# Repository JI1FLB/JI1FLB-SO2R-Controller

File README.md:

# JI1FLB-SO2R-Controller

This JI1FLB SO2R box (controller) is a tool for amateur radio contest and works with OTRPS protocol.
This device controls two amateur radio rigs and is programmed with Arduino UNO sketch.
Hardware was composed of circuits that are easily available at electronic parts stores.
In addition, each circuit is designed to PCB to ensure ease of manufacture and product stability.

This JI1FLB　SO2R box (controller) provides software and hardware as freeware subject to non-commercial use.
Hardware PCB board is scheduled to provide KiCAD data subject to non-commercial use after completion of reprocessing.
I will supply the PCB to those who need it, with shipping fee and very cheap actual expenses. 
However, some consideration is required when installing some parts.

このJI1FLB　SO2Rボックス（コントローラ）は、アマチュア無線コンテスト用ツールでOTRPSプロトコロルで動作します。
この装置は、2台のアマチュア無線リグをコントロールするもので、ArduinoUNOのスケッチでプログラムされています。
ハードウェアは、電子パーツ店で容易に入手可能な部品で回路を構成しました。
また、各回路は、製作の容易性、製品の安定性を確保するため、PCB化を図っています。

このJI1FLB　SO2Rボックス（コントローラ）は、非商用利用を条件にソフトウェアとハードウェアをフリーウェアとして提供します。
ハードウェアのPCB基板は、KiCADデータを再作が完了後に、非商用利用を条件に提供する予定です。
私は、PCBを必要な方に、送料と非常に安価な実費で供給します。ただし、一部の部品を取り付け際に若干の考慮が必要です。

2018/11/18 Seiichi Tanaka 田中盛一

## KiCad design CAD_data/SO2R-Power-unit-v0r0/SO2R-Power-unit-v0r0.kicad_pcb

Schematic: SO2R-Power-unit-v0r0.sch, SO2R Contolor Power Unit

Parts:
C1, C5: 100uF; C_Radial_D10_L13_P5
C2, C3, C6, C7: 0.1uF; C_Rect_L7_W2_P5
C4: 56uF 25SEPF56M; C_Radial_D6.3_L11.2_P2.5
C8: 56uF; C_Radial_D6.3_L11.2_P2.5
D1: LED; LED-3MM
D6, D7: 1N4007; Diode_DO-41_SOD81_Horizontal_RM10
F1: RUEF185; C_Rect_L7_W3.5_P5
F2, F3: RXEF065; C_Rect_L7_W3.5_P5
F4, F5: RXEF110; C_Rect_L7_W3.5_P5
FI1: EMI_FILTER2; EMIFILTER
P1, P2, P3, P4, P5: CONN_01X02; CON-JST-B02B-XASK-1
R1: 2.2K; Resistor_Horizontal_RM7mm
U1, U2: LM7805CT; TO-220
VAR1: CNR07D151K; RV_Disc_D7_W3.4_P5
W1, W2, W3, W4, W5: TEST_1P; SolderWirePad_single_0-8mmDrill

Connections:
GND: C1.2, C2.2, C3.2, C4.2, C5.2, C6.2, C7.2, C8.2, D1.1 (K), FI1.2 (GND), P1.2, P2.2, P3.2, P4.2, P5.2, U1.2 (GND), U2.2 (GND), VAR1.2
unnamed: C1.1, C2.1, C5.1, C6.1, D6.1, D7.1, F5.1, FI1.3 (VO), U1.1 (IN), U2.1 (IN)
unnamed: C3.1, C4.1, D6.2, F2.1, F3.1, U1.3 (OUT)
unnamed: C7.1, C8.1, D7.2, F4.1, U2.3 (OUT)
unnamed: D1.2 (A), R1.2
unnamed: F1.1, P1.1
unnamed: F1.2, FI1.1 (VI), R1.1, VAR1.1, W1.1
unnamed: F2.2, P2.1, W2.1
unnamed: F3.2, P3.1, W3.1
unnamed: F4.2, P4.1, W4.1
unnamed: F5.2, P5.1, W5.1

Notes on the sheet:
7.62mm
8.89mm

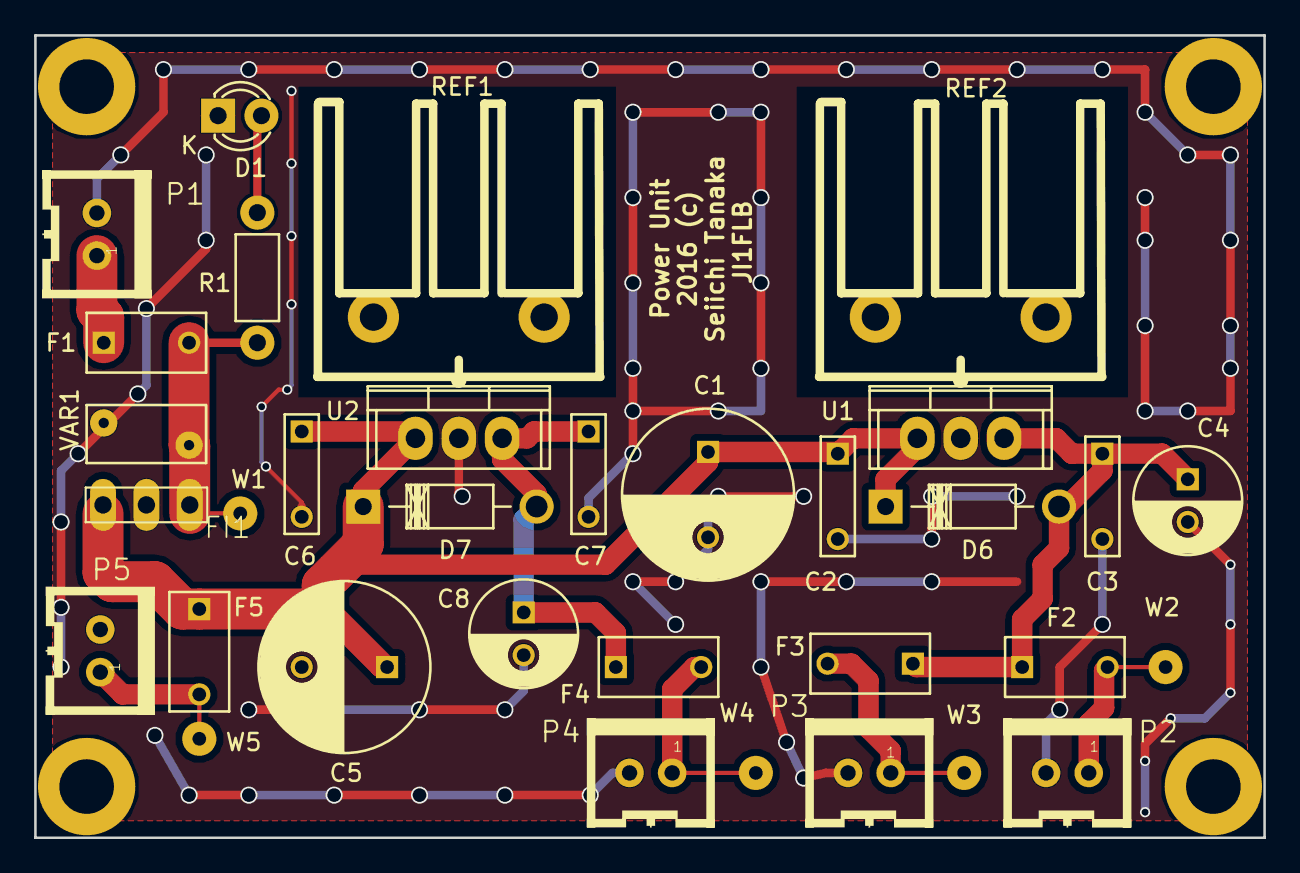
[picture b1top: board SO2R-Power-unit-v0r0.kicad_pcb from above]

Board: 2 copper layers, 72.0 x 47.0 mm, 33 parts (0 on the bottom side), 11 nets.

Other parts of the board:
REF1, REF2: Heatsink-16PB017

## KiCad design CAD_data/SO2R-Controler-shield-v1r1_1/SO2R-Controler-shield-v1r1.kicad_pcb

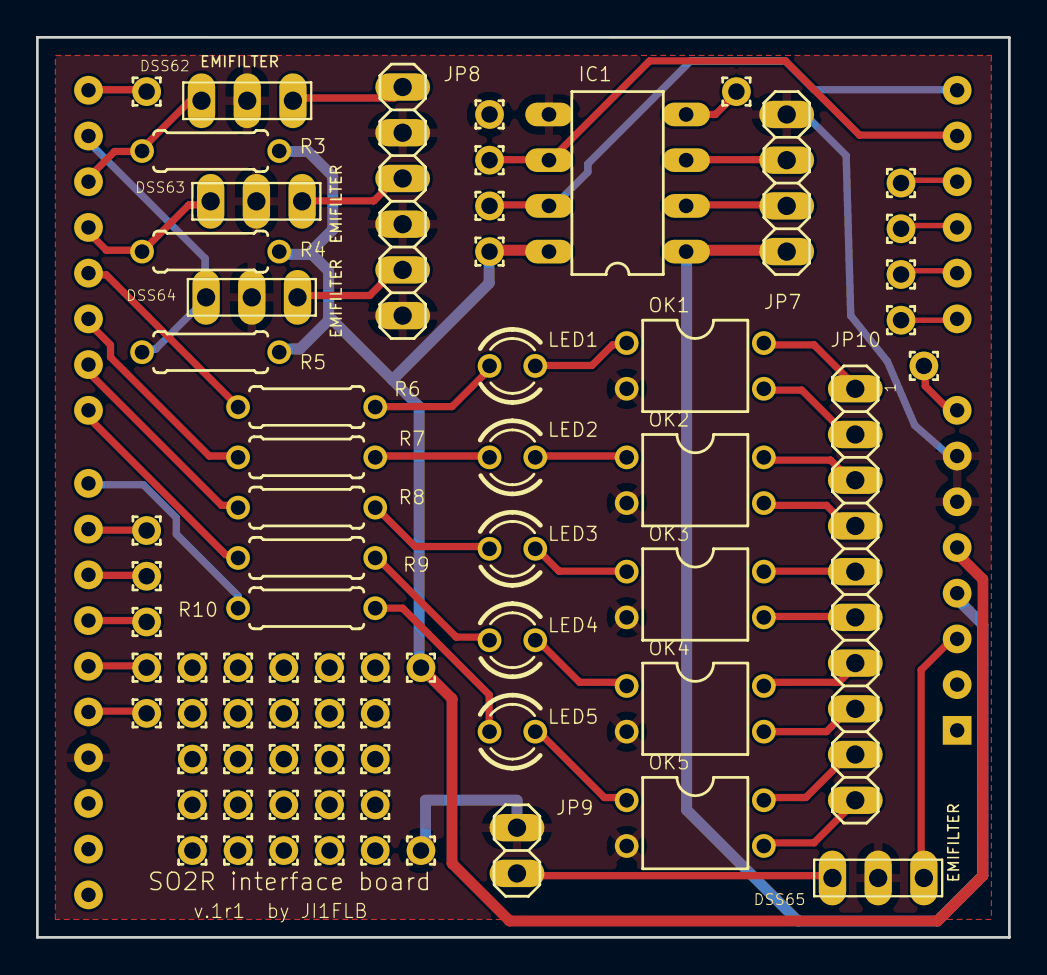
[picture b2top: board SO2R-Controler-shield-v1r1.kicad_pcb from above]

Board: 2 copper layers, 54.0 x 50.0 mm, 71 parts (0 on the bottom side), 52 nets.

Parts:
A1: Arduino_UNO_R3
DSS62, DSS63, DSS64, DSS65: EMIFILTER
IC1: AE-PCA9306; DIL8
JP7: I2C LCD; 1X04
JP8: Force Switch; 1X06
JP9: RESET; 1X02
JP10: Isolate port; 1X10
LED1, LED2, LED3, LED4, LED5: OSDR3133A; LED3MM
OK1, OK2, OK3, OK4, OK5: TLP621; DIL04
PAD1, PAD2, PAD3, PAD4, PAD5, PAD6, PAD7, PAD8, PAD9, PAD10, PAD11, PAD12, PAD13, PAD14, PAD15, PAD16, PAD17, PAD18, PAD19, PAD20, PAD21, PAD22, PAD23, PAD24, PAD25, PAD26, PAD27, PAD28, PAD29, PAD30, PAD31, PAD32, PAD33, PAD34, PAD35, PAD36, PAD37, PAD38, PAD39, PAD40, PAD41, PAD42, PAD43: 1,6_0,9
R3, R4, R5: 10K; 0207_7
R6, R7, R8, R9, R10: 330; 0207_7

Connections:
+3V3: A1.4, IC1.1, JP7.1
/D1: A1.16, DSS64.3, R5.1
/D2: A1.17, DSS62.3, R3.1
/D3: A1.18, DSS63.3, R4.1
/D4: A1.19, R6.1
/D5: A1.20, R7.1
/D6: A1.21, R8.1
/D7: A1.22, R9.1
/D8: A1.23, R10.1
/SCL5V: A1.14, IC1.7, PAD4.1
/SDA5V: A1.13, IC1.6, PAD5.1
GND1: A1.6, A1.7, A1.29, DSS62.2, DSS63.2, DSS64.2, DSS65.2, IC1.5, JP7.4, JP8.2, JP8.4, JP8.6, JP9.2, OK1.2, OK2.2, OK3.2, OK4.2, OK5.2, PAD6.1, PAD39.1
unnamed: A1.8, PAD1.1
unnamed: A1.9, PAD40.1
unnamed: A1.10, PAD41.1
unnamed: A1.11, PAD42.1
unnamed: A1.12, PAD43.1
unnamed: A1.15, PAD12.1
unnamed: A1.24, PAD11.1
unnamed: A1.25, PAD10.1
unnamed: A1.26, PAD9.1
unnamed: A1.27, PAD8.1
unnamed: A1.28, PAD7.1
unnamed: DSS62.1, JP8.1
unnamed: DSS63.1, JP8.3
unnamed: DSS64.1, JP8.5
unnamed: DSS65.1, JP9.1
unnamed: IC1.2, JP7.2
unnamed: IC1.3, JP7.3
unnamed: IC1.4, PAD2.1
unnamed: JP10.1, OK1.4
unnamed: JP10.2, OK1.3
unnamed: JP10.3, OK2.4
unnamed: JP10.4, OK2.3
unnamed: JP10.5, OK3.4
unnamed: JP10.6, OK3.3
unnamed: JP10.7, OK4.4
unnamed: JP10.8, OK4.3
unnamed: JP10.9, OK5.4
unnamed: JP10.10, OK5.3
unnamed: LED1.A, R6.2
unnamed: LED1.K, OK1.1
unnamed: LED2.A, R7.2
unnamed: LED2.K, OK2.1
unnamed: LED3.A, R8.2
unnamed: LED3.K, OK3.1
unnamed: LED4.A, R9.2
unnamed: LED4.K, OK4.1
unnamed: LED5.A, R10.2
unnamed: LED5.K, OK5.1
RESET: A1.3, DSS65.3
VCC: A1.5, IC1.8, PAD3.1, PAD38.1, R3.2, R4.2, R5.2

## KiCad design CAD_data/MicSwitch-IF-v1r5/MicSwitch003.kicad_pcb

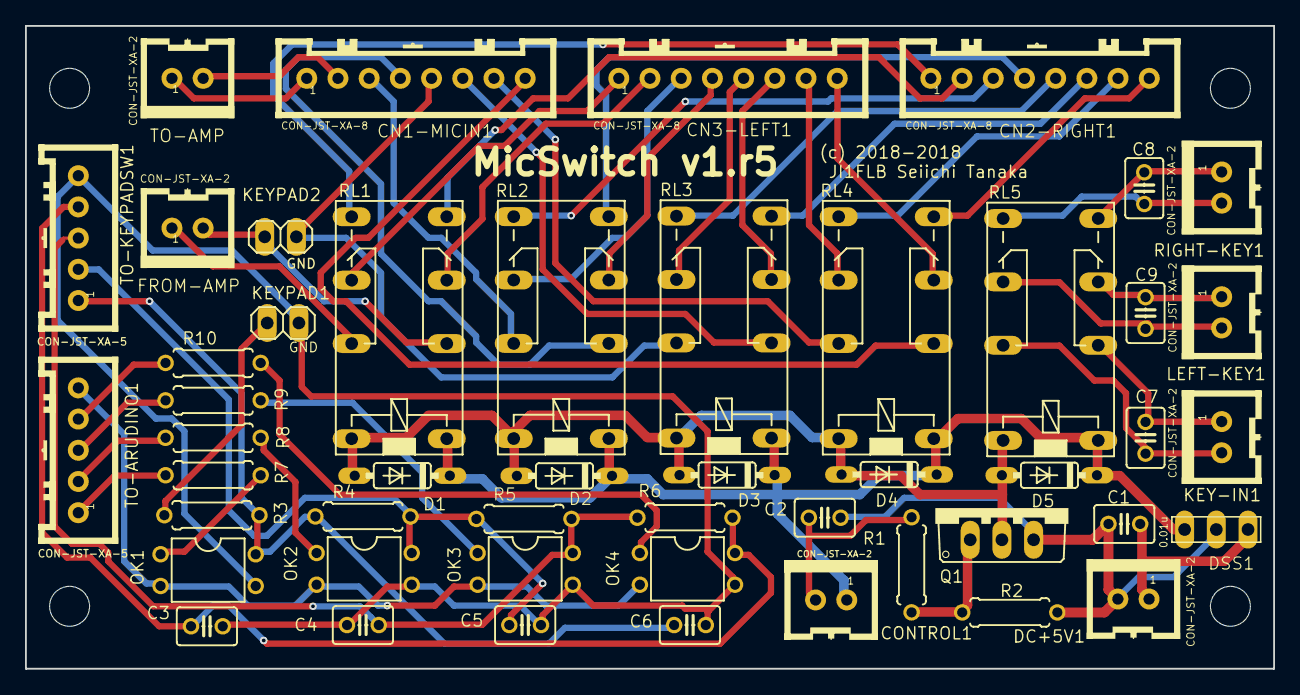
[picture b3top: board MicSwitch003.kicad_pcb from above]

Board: 2 copper layers, 100.0 x 51.5 mm, 49 parts (0 on the bottom side), 53 nets.

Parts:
C1, C2, C3, C4, C5, C6, C7, C8, C9: 0.01; C025-030X050
CN1-MICIN1, CN2-RIGHT1, CN3-LEFT1: CON-JST-XA-8; CON-JST-B08B-XASK-1
CONTROL1: CON-JST-XA-2; CON-JST-B02B-XASK-1
D1, D2, D3, D4, D5: 1N4148; DO35-7
DC+5V1: CON-JST-XA-2; CON-JST-B02B-XASK-1
DSS1: 0.01u; EMIFILTER
FROM-AMP: CON-JST-XA-2; CON-JST-B02B-XASK-1
KEY-IN1: CON-JST-XA-2; CON-JST-B02B-XASK-1
KEYPAD1, KEYPAD2: PINHD-1X2; 1X02
LEFT-KEY1: CON-JST-XA-2; CON-JST-B02B-XASK-1
OK1, OK2, OK3, OK4: TLP222AF; DIL04
Q1: 2SK4017; TO220BV
R1: 33; 0207_7
R2: 10K; 0207_7
R3, R4: 1.5k; 0207_7
R5: 2.2k; 0207_7
R6: 4.7k; 0207_7
R7, R8, R9, R10: 480; 0207_7
RIGHT-KEY1: CON-JST-XA-2; CON-JST-B02B-XASK-1
RL1, RL2, RL3, RL4, RL5: 941H-2C-5D; 351
TO-AMP: CON-JST-XA-2; CON-JST-B02B-XASK-1
TO-ARUDINO1: CON-JST-XA-5; CON-JST-B05B-XASK-1
TO-KEYPADSW1: CON-JST-XA-5; CON-JST-B05B-XASK-1

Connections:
+5V: CONTROL1.1, D1.C, D2.C, D3.C, D4.C, D5.C, DSS1.3, RL1.1, RL2.1, RL3.1, RL4.1, RL5.1
GND: C1.2, C2.2, DC+5V1.2, DSS1.2, Q1.S, R2.1
unnamed: C1.1, DC+5V1.1, DSS1.1
unnamed: C2.1, CONTROL1.2, R1.2
unnamed: C3.1, OK4.4, R6.2, TO-KEYPADSW1.4
unnamed: C3.2, C4.2, C5.2, C6.2, KEYPAD1.2, OK1.3, OK2.3, OK3.3, OK4.3, TO-KEYPADSW1.5
unnamed: C4.1, OK3.4, R5.2, R6.1, TO-KEYPADSW1.3
unnamed: C5.1, OK2.4, R4.2, R5.1, TO-KEYPADSW1.2
unnamed: C6.1, OK1.4, R3.2, R4.1, TO-KEYPADSW1.1
unnamed: C7.1, KEY-IN1.1, RL5.P1
unnamed: C7.2, KEY-IN1.2, RL5.P2
unnamed: C8.1, RIGHT-KEY1.1, RL5.S1
unnamed: C8.2, RIGHT-KEY1.2, RL5.S2
unnamed: C9.1, LEFT-KEY1.1, RL5.O1
unnamed: C9.2, LEFT-KEY1.2, RL5.O2
unnamed: CN1-MICIN1.1, TO-AMP.1
unnamed: CN1-MICIN1.2, TO-AMP.2
unnamed: CN1-MICIN1.3, RL2.P2
unnamed: CN1-MICIN1.4, RL2.P1
unnamed: CN1-MICIN1.5, KEYPAD2.1, RL3.P2
unnamed: CN1-MICIN1.6, RL3.P1
unnamed: CN1-MICIN1.7, RL4.P2
unnamed: CN1-MICIN1.8, RL4.P1
unnamed: CN2-RIGHT1.1, RL1.S2
unnamed: CN2-RIGHT1.2, RL1.S1
unnamed: CN2-RIGHT1.3, RL2.S2
unnamed: CN2-RIGHT1.4, RL2.S1
unnamed: CN2-RIGHT1.5, RL3.S2
unnamed: CN2-RIGHT1.6, RL3.S1
unnamed: CN2-RIGHT1.7, RL4.S2
unnamed: CN2-RIGHT1.8, RL4.S1
unnamed: CN3-LEFT1.1, RL1.O2
unnamed: CN3-LEFT1.2, RL1.O1
unnamed: CN3-LEFT1.3, RL2.O2
unnamed: CN3-LEFT1.4, RL2.O1
unnamed: CN3-LEFT1.5, RL3.O2
unnamed: CN3-LEFT1.6, RL3.O1
unnamed: CN3-LEFT1.7, RL4.O2
unnamed: CN3-LEFT1.8, RL4.O1
unnamed: D1.A, D2.A, D3.A, D4.A, D5.A, Q1.D, RL1.16, RL2.16, RL3.16, RL4.16, RL5.16
unnamed: FROM-AMP.1, RL1.P2
unnamed: FROM-AMP.2, KEYPAD2.2, RL1.P1
unnamed: KEYPAD1.1, R3.1
unnamed: OK1.1, R7.2
unnamed: OK1.2, OK2.2, OK3.2, OK4.2, TO-ARUDINO1.5
unnamed: OK2.1, R8.2
unnamed: OK3.1, R9.2
unnamed: OK4.1, R10.2
unnamed: Q1.G, R1.1, R2.2
unnamed: R7.1, TO-ARUDINO1.1
unnamed: R8.1, TO-ARUDINO1.2
unnamed: R9.1, TO-ARUDINO1.3
unnamed: R10.1, TO-ARUDINO1.4

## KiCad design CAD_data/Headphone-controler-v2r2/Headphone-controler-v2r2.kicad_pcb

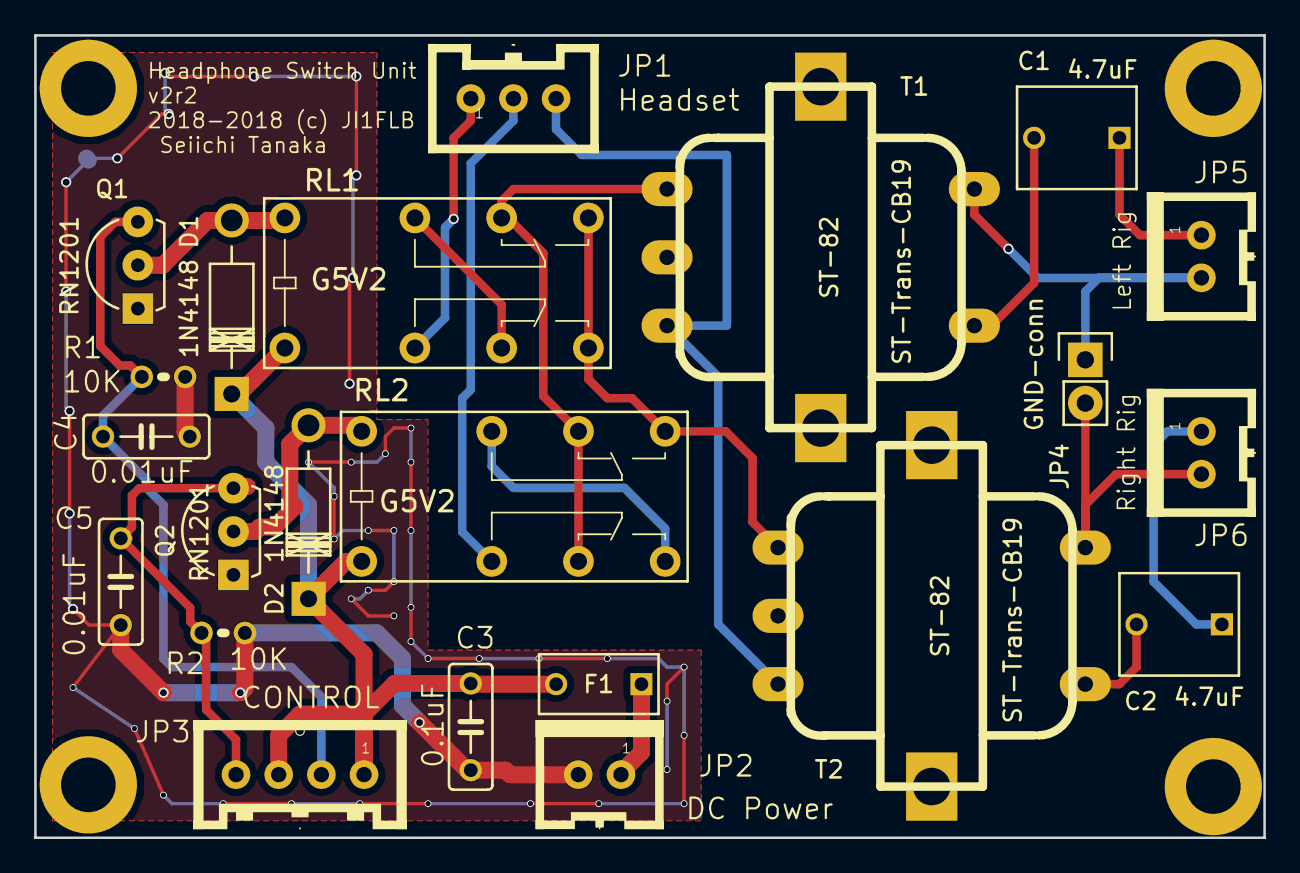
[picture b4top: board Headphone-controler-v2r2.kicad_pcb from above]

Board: 2 copper layers, 72.0 x 47.0 mm, 22 parts (0 on the bottom side), 20 nets.

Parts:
C1, C2: 4.7uF; C_Rect_L7_W6_P5
C3: 0.1uF; C050-025X075
C4, C5: 0.01uF; C050-025X075
D1, D2: 1N4148; Diode_DO-41_SOD81_Horizontal_RM10
F1: Poli FUSE; C_Rect_L7_W3.5_P5
JP1: Headset; CON-JST-B03B-XASK-1
JP2: DC Power; CON-JST-B02B-XASK-1
JP3: CONTROL; CON-JST-B04B-XASK-1
JP4: GND-conn; Pin_Header_Straight_1x02
JP5: Left Rig; CON-JST-B02B-XASK-1
JP6: Right Rig; CON-JST-B02B-XASK-1
Q1, Q2: RN1201; 2SC1815GR
R1, R2: 10K; 0204V
RL1, RL2: G5V2; G5V-2
T1, T2: ST-82; ST-Trans-CB19

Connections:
+5V: C3.1, D1.1, D2.1, F1.2, JP3.1, JP3.3, RL1.1, RL2.1
GND: C3.2, C4.2, C5.2, JP2.2, Q1.1, Q2.1, R1.2, R2.2
unnamed: C1.1, JP5.1
unnamed: C1.2, T1.5
unnamed: C2.1, JP6.1
unnamed: C2.2, T2.5
unnamed: C4.1, JP3.2, Q1.3, R1.1
unnamed: C5.1, JP3.4, Q2.3, R2.1
unnamed: D1.2, Q1.2, RL1.16
unnamed: D2.2, Q2.2, RL2.16
unnamed: F1.1, JP2.1
unnamed: JP1.1, RL1.4
unnamed: JP1.2, RL2.4
unnamed: JP1.3, T1.1, T2.1
unnamed: JP4.1, JP5.2, T1.4
unnamed: JP4.2, JP6.2, T2.4
unnamed: RL1.8, RL1.9, RL2.9, T2.3
unnamed: RL1.11, RL2.6, RL2.11, T1.3
unnamed: RL1.6, RL1.13
unnamed: RL2.8, RL2.13

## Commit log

2017-12-24 General outline documents
    This documents appears JI1FLB's SO2R Controller features.
2017-12-25 Sketch for JI1FLB's SO2R controller
    Sketch infomation
    vertion:0
    revion:8
    patch:3
2017-12-26 Create LICENSE
2018-11-18 SO2R Box Sketch
2018-11-18 CAD_data
2018-11-18 JI1FLB SO2R Box sketch
2018-11-18 PCB_size_image
2018-11-18 Schematics_image

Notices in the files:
CAD_data/MicSwitch-IF-v1r5/MicSwitch003.kicad_pcb:
(c) 2018-2018
